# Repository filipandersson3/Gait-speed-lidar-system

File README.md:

# Gait speed lidar system
Lidar system for measuring walking speed using a Garmin LIDAR-Lite v3. 

It records distance over time for a person walking in front of a lidar. This data is stored on the device until it gets extracted over USB using a python program.

This repo contains the KiCAD project, code for the microcontroller and python code for data extraction. It also contains measurement data.

This is related to my thesis project, you can find more information [here.](https://urn.kb.se/resolve?urn=urn:nbn:se:umu:diva-240602)

F. Andersson, “In-home gait speed measurement using lidar,” Dissertation, 2025.

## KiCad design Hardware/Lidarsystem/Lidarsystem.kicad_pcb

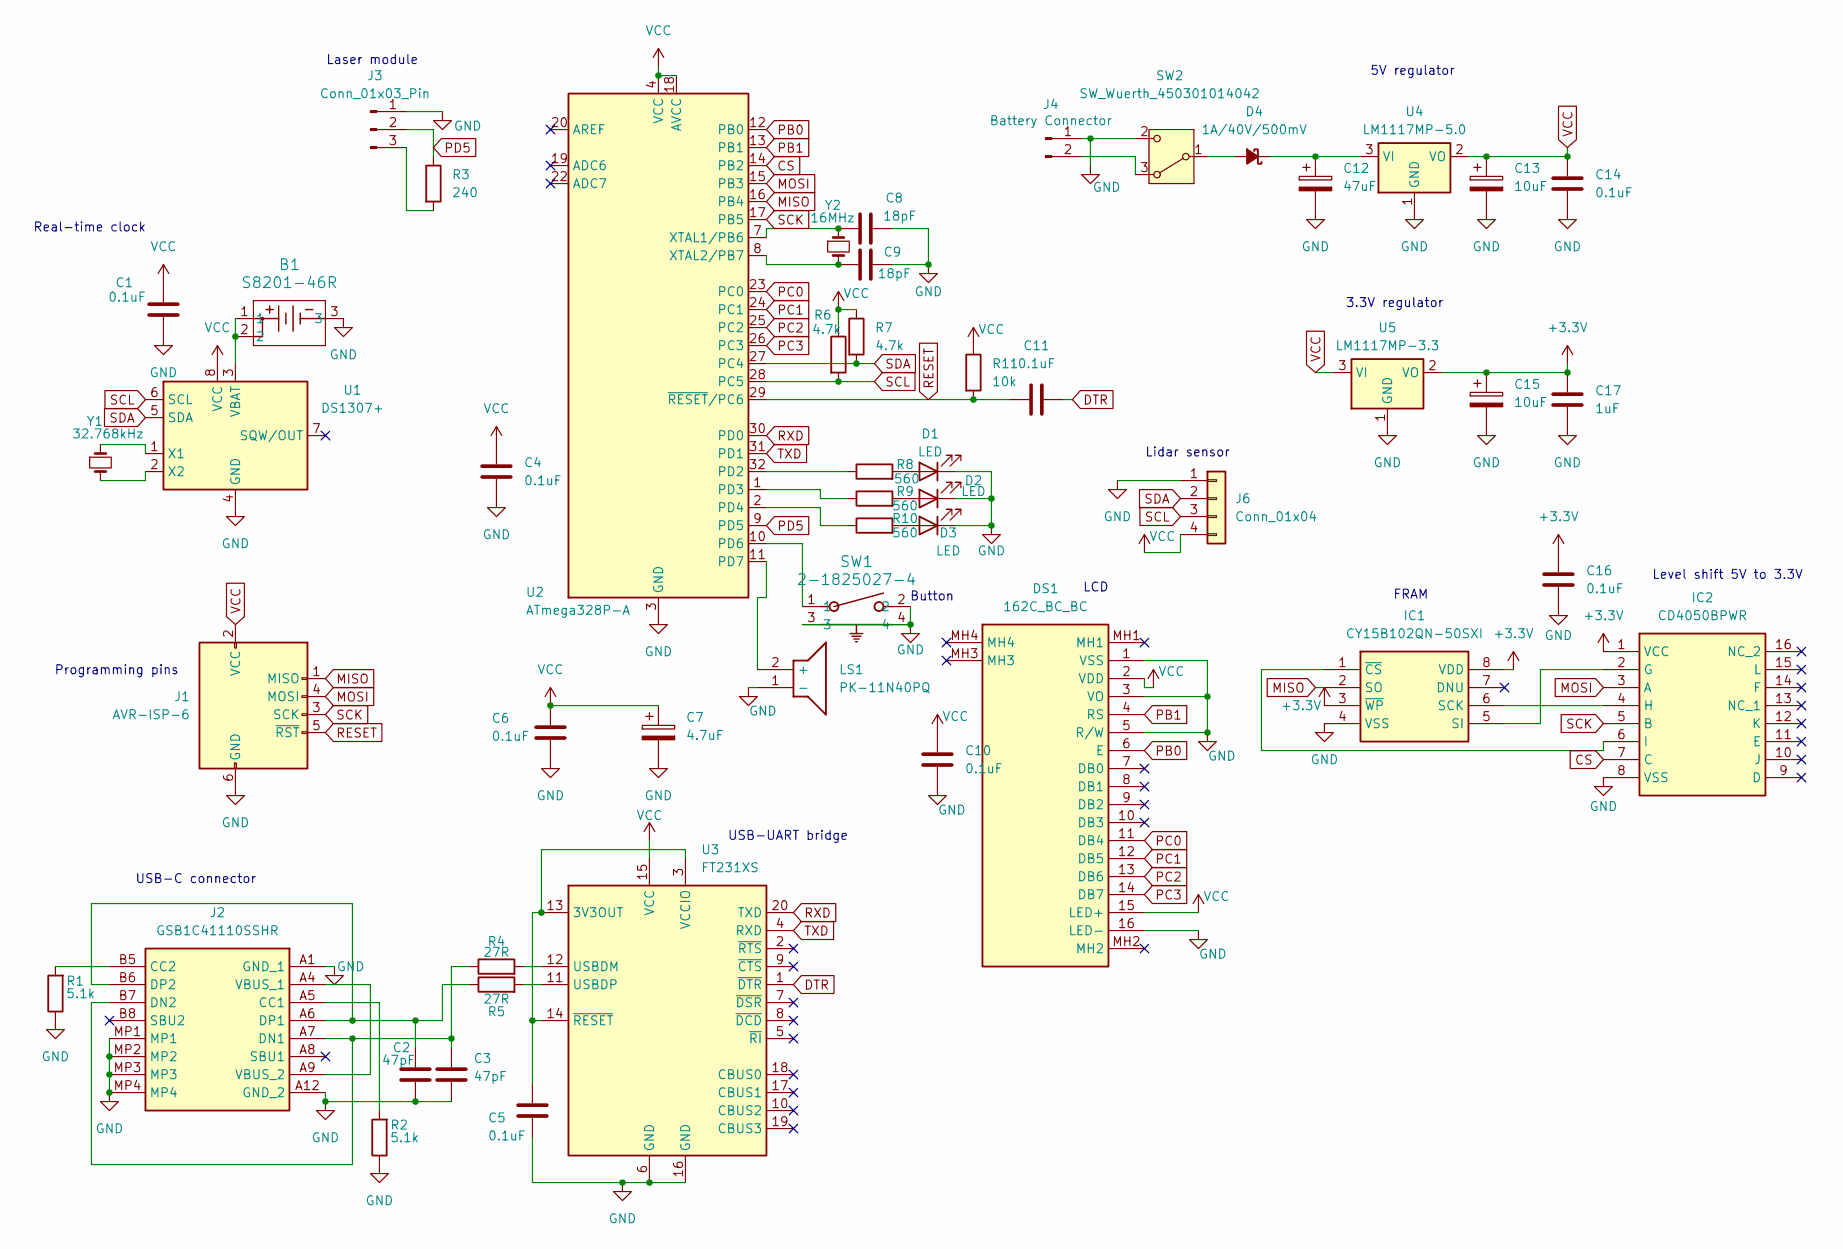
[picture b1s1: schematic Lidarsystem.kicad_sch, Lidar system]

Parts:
B1: S8201-46R; S8201-46R_HRW
C1, C4, C5, C6, C10, C11, C14, C16: 0.1uF; C_0805_2012Metric_Pad1.18x1.45mm_HandSolder
C2, C3: 47pF; C_0805_2012Metric_Pad1.18x1.45mm_HandSolder
C7: 4.7uF; CP_EIA-6032-15_Kemet-U_HandSolder
C8, C9: 18pF; C_0805_2012Metric_Pad1.18x1.45mm_HandSolder
C12: 47uF; CP_EIA-6032-15_Kemet-U_HandSolder
C13, C15: 10uF; CP_EIA-6032-15_Kemet-U_HandSolder
C17: 1uF; C_0805_2012Metric_Pad1.18x1.45mm_HandSolder
D1, D2, D3: LED; PinHeader_1x02_P2.54mm_Horizontal
D4: 1A/40V/500mV; D_3220_8050Metric_Pad2.65x5.15mm_HandSolder
DS1: 162C_BC_BC; 162CBCBC; Mouser Part Number 758-162CBCBC
IC1: CY15B102QN-50SXI; DIP-8_W7.62mm_Socket_LongPads; Mouser Part Number 727-CY15B102QN-50SXI
IC2: CD4050BPWR; SOP65P640X120-16N; Mouser Part Number 595-CD4050BPWR
J1: AVR-ISP-6; IDC-Header_2x03_P2.54mm_Vertical
J2: GSB1C41110SSHR; Manufacturer_Part_Number GSB1C41110SSHR
J3: Conn_01x03_Pin; PinHeader_1x03_P2.54mm_Vertical
J4: Battery Connector; SolderWire-0.15sqmm_1x02_P4mm_D0.5mm_OD1.5mm
J6: Conn_01x04; PinHeader_1x04_P2.54mm_Horizontal
LS1: PK-11N40PQ; PK11N40PQ; Mouser Part Number 539-PK-11N40PQ
R1, R2: 5.1k; R_0805_2012Metric_Pad1.20x1.40mm_HandSolder
R3: 240; R_0805_2012Metric_Pad1.20x1.40mm_HandSolder
R4, R5: 27R; R_0805_2012Metric_Pad1.20x1.40mm_HandSolder
R6, R7: 4.7k; R_0805_2012Metric_Pad1.20x1.40mm_HandSolder
R8, R9, R10: 560; R_0805_2012Metric_Pad1.20x1.40mm_HandSolder
R11: 10k; R_0805_2012Metric_Pad1.20x1.40mm_HandSolder
SW1: 2-1825027-4; SW2_1825027-H_TEC
SW2: SW_Wuerth_450301014042; SW_Slide-03_Wuerth-WS-SLTV_10x2.5x6.4_P2.54mm
U1: DS1307+; SOIC-8_3.9x4.9mm_P1.27mm
U2: ATmega328P-A; TQFP-32_7x7mm_P0.8mm
U3: FT231XS; SSOP-20_3.9x8.7mm_P0.635mm
U4: LM1117MP-5.0; SOT-223-3_TabPin2
U5: LM1117MP-3.3; SOT-223-3_TabPin2
Y1: 32.768kHz; Crystal_Round_D3.0mm_Vertical
Y2: 16MHz; Crystal_SMD_Abracon_ABM3-2Pin_5.0x3.2mm_HandSoldering

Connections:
+3.3V: C15.1, C16.1, C17.1, IC1.3 (~WP), IC1.8 (VDD), IC2.1 (VCC), U5.2 (VO)
CS: IC2.7 (C), U2.14 (PB2)
DTR: C11.1, U3.1 (~DTR)
GND: B1.3, C1.2, C2.2, C3.2, C4.2, C5.2, C6.2, C7.2, C8.1, C9.1, C10.2, C12.2, C13.2, C14.2, C15.2, C16.2, C17.2, D1.1 (K), D2.1 (K), D3.1 (K), DS1.1 (VSS), DS1.3 (VO), DS1.5 (R/W), DS1.16 (LED-), IC1.4 (VSS), IC2.8 (VSS), J1.6 (GND), J2.A1 (GND_1), J2.A12 (GND_2), J2.MP1, J2.MP2, J2.MP3, J2.MP4, J3.1, J4.1, J6.1, LS1.1 (-), R1.1, R2.1, SW1.2, SW1.3, SW1.4, SW2.2 (C), U1.4 (GND), U2.3 (GND), U2.5 (GND), U2.21 (GND), U3.6 (GND), U3.16 (GND), U4.1 (GND), U5.1 (GND)
MISO: IC1.2 (SO), J1.1 (MISO), U2.16 (PB4)
MOSI: IC2.3 (A), J1.4 (MOSI), U2.15 (PB3)
unnamed: D1.2 (A), R8.2
unnamed: D2.2 (A), R9.2
unnamed: D3.2 (A), R10.2
unnamed: D4.2 (A), SW2.1 (B)
unnamed: C12.1, D4.1 (K), U4.3 (VI)
unnamed: IC1.6 (SCK), IC2.4 (H)
unnamed: IC1.5 (SI), IC2.2 (G)
unnamed: IC1.1 (~CS), IC2.6 (I)
unnamed: J2.A5 (CC1), R2.2
unnamed: J2.B5 (CC2), R1.2
unnamed: C3.1, J2.A7 (DN1), J2.B7 (DN2), R4.1
unnamed: C2.1, J2.A6 (DP1), J2.B6 (DP2), R5.1
unnamed: J2.A4 (VBUS_1), J2.A9 (VBUS_2)
unnamed: J3.3, R3.2
unnamed: J4.2, SW2.3 (A)
unnamed: LS1.2 (+), U2.11 (PD7)
unnamed: B1.1, B1.2, U1.3 (VBAT)
unnamed: U1.1 (X1), Y1.1
unnamed: U1.2 (X2), Y1.2
unnamed: R8.1, U2.32 (PD2)
unnamed: R9.1, U2.1 (PD3)
unnamed: R10.1, U2.2 (PD4)
unnamed: SW1.1, U2.10 (PD6)
unnamed: C8.2, U2.7 (XTAL1/PB6), Y2.1
unnamed: C9.2, U2.8 (XTAL2/PB7), Y2.2
unnamed: C5.1, U3.3 (VCCIO), U3.13 (3V3OUT), U3.14 (~RESET)
unnamed: R4.2, U3.12 (USBDM)
unnamed: R5.2, U3.11 (USBDP)
PB0: DS1.6 (E), U2.12 (PB0)
PB1: DS1.4 (RS), U2.13 (PB1)
PC0: DS1.11 (DB4), U2.23 (PC0)
PC1: DS1.12 (DB5), U2.24 (PC1)
PC2: DS1.13 (DB6), U2.25 (PC2)
PC3: DS1.14 (DB7), U2.26 (PC3)
PD5: J3.2, R3.1, U2.9 (PD5)
RESET: C11.2, J1.5 (~RST), R11.2, U2.29 (~RESET/PC6)
RXD: U2.30 (PD0), U3.20 (TXD)
SCK: IC2.5 (B), J1.3 (SCK), U2.17 (PB5)
SCL: J6.3, R6.2, U1.6 (SCL), U2.28 (PC5)
SDA: J6.2, R7.2, U1.5 (SDA), U2.27 (PC4)
TXD: U2.31 (PD1), U3.4 (RXD)
VCC: C1.1, C4.1, C6.1, C7.1, C10.1, C13.1, C14.1, DS1.2 (VDD), DS1.15 (LED+), J1.2 (VCC), J6.4, R6.1, R7.1, R11.1, U1.8 (VCC), U2.4 (VCC), U2.6 (VCC), U2.18 (AVCC), U3.15 (VCC), U4.2 (VO), U5.3 (VI)

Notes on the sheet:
Real-time clock
5V regulator
FRAM
Level shift 5V to 3.3V
USB-UART bridge
Programming pins
Lidar sensor
USB-C connector
LCD
3.3V regulator
Laser module
Button

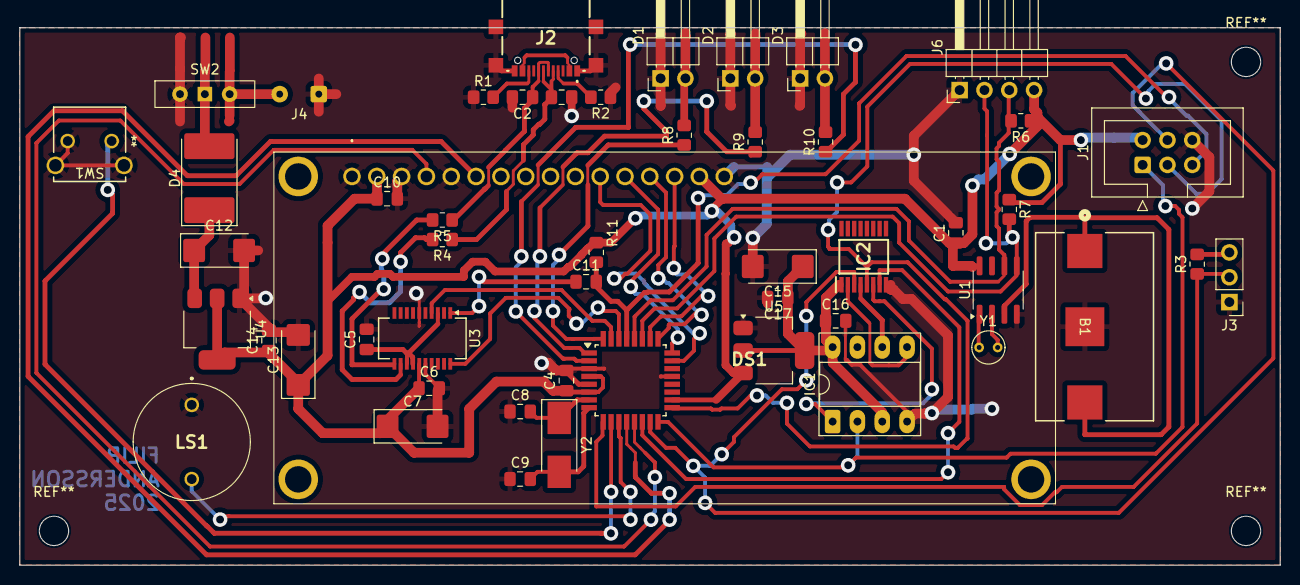
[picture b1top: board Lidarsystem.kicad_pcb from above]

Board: 2 copper layers, 129.0 x 55.0 mm, 51 parts (0 on the bottom side), 48 nets.
